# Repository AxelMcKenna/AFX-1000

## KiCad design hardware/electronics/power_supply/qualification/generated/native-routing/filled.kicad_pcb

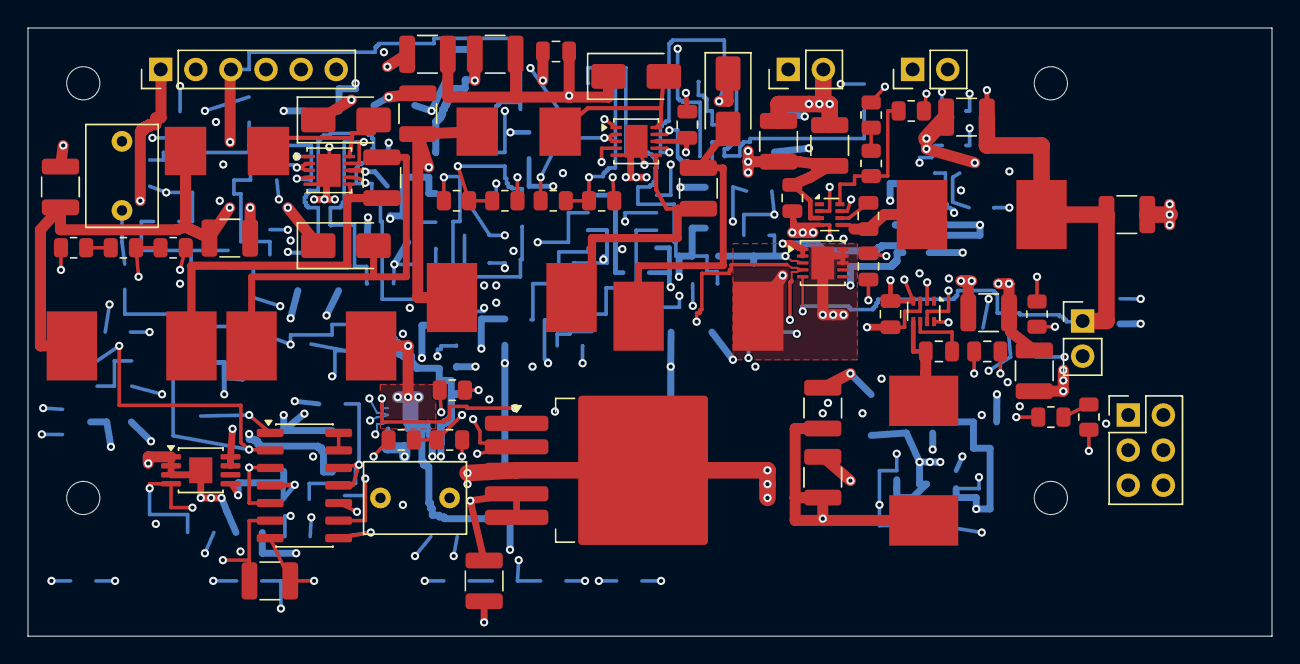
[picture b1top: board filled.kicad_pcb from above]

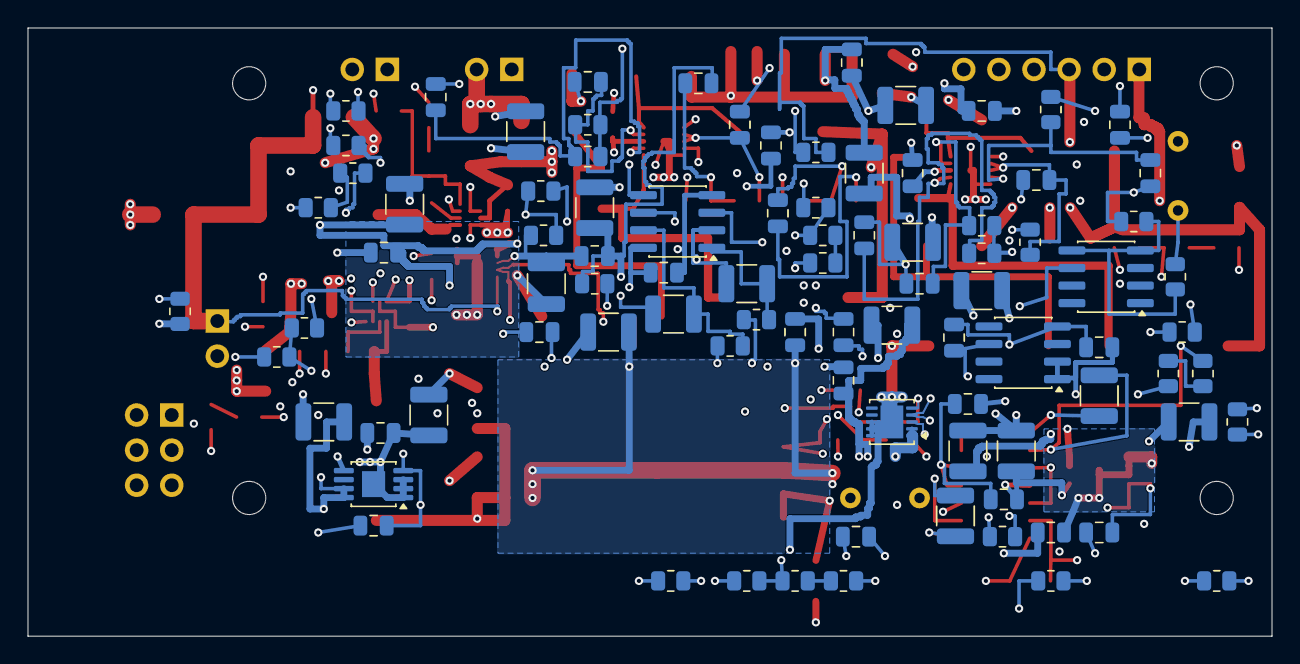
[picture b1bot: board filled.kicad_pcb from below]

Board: 6 copper layers, 90.0 x 44.0 mm, 161 parts (89 on the bottom side), 67 nets.

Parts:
C1, C63: 10uF 63V X7R; C_1210_3225Metric
C2, C3, C5, C6, C8, C9, C37, C42, C47, C52, C57, C64, C65, C67, C68, C70: 22uF 50V X7R; C_1210_3225Metric
C4, C7, C10, C22, C29, C35, C38, C40, C43, C45, C48, C50, C53, C55, C58, C59, C61, C66, C69, C71: 100nF 50V X7R; C_0805_2012Metric
C11, C16, C23, C30, C72: 100nF 16V X7R; C_0805_2012Metric
C12, C14, C73, C75: 68pF 50V C0G 5%; C_0805_2012Metric
C13, C15, C74, C76: 330nF 16V X7R; C_0805_2012Metric
C17: 1uF 16V X7R; C_0805_2012Metric
C18, C19, C25, C26: 22uF 16V X7R; C_1210_3225Metric
C20, C21, C27, C28: 10uF 25V X7R; C_1210_3225Metric
C24: 33nF 16V X7R; C_0805_2012Metric
C31: 2.2uF 16V X7R; C_0805_2012Metric
C32, C33: 1uF film 63V 10% MKS2C041001F00KSSD; C_Rect_L7.2mm_W5.0mm_P5.00mm
C34, C39, C44, C49, C54: 47nF 50V C0G 5%; C_1210_3225Metric
C36, C41, C46, C51, C56: 10uF 50V X7R; C_1210_3225Metric
C60, C62: 1uF 50V X7R; C_0805_2012Metric
D1, D2, D3, D4: SS16-E3/61T; D_SMA
H1, H2, H3, H4: M2_CLEARANCE; M2_Clearance
J1, J3, J5: Header2; PinHeader_1x02_P2.54mm_Vertical
J2: Header6; PinHeader_1x06_P2.54mm_Vertical
J4: Header6; PinHeader_2x03_P2.54mm_Vertical
L1, L6: 33uH 20% SRP7050WA-330M; SRP7050WA
L2, L3, L7, L8: 68uH 20% SRP1050WA-680M; SRP1050WA
L4, L5: 10uH 20% SRP1050WA-100M; SRP1050WA
R1: 300k 0.01% 5ppm; R_0805_2012Metric
R2, R3, R4, R45, R46: 15k 0.01% 5ppm; R_0805_2012Metric
R5, R20, R21, R34, R35: 330k 0.01% 5ppm; R_0805_2012Metric
R6, R7, R49, R50: 4.7k 1%; R_0805_2012Metric
R8, R12: 10k 1%; R_0805_2012Metric
R9, R13: 22k 1%; R_0805_2012Metric
R10: 10.5k 0.01% 5ppm; R_0805_2012Metric
R11, R16: 2k 0.01% 5ppm; R_0805_2012Metric
R14: 12.4k 0.01% 5ppm; R_0805_2012Metric
R15: 100 0.01% 5ppm; R_0805_2012Metric
R17, R19: 1k 1%; R_0805_2012Metric
R18: 100k 1%; R_0805_2012Metric
R22, R27, R30, R31, R36, R41: 100k 0.01% 5ppm; R_0805_2012Metric
R23, R28, R32, R37, R42: 6.8k 1%; R_0805_2012Metric
R24, R38: 9.09k 1%; R_0805_2012Metric
R25, R39, R47: 200k 0.01% 5ppm; R_0805_2012Metric
R26, R40: 180k 0.01% 5ppm; R_0805_2012Metric
R29, R43: 5.62k 1%; R_0805_2012Metric
R33: 2.21k 1%; R_0805_2012Metric
R44: 240k 0.01% 5ppm; R_0805_2012Metric
R48: 54.9k 0.01% 5ppm; R_0805_2012Metric
R51: 10 0.01% 5ppm; R_0805_2012Metric
U1, U13: LT3471EDD#PBF; DFN-10-1EP_3x3mm_P0.5mm_EP1.65x2.38mm
U2, U3: TPS62933FDRLR; SOT-583-8
U4: REF5025EIDR; SOIC-8_3.9x4.9mm_P1.27mm
U5: OPA4192ID; SOIC-14_3.9x8.7mm_P1.27mm
U6: OPA2192ID; SOIC-8_3.9x4.9mm_P1.27mm
U7, U9: LT3080IMS8E#PBF; MSOP-8-1EP_3x3mm_P0.65mm_EP1.68x1.88mm
U8: LT3080IQ#PBF; TO-263-5_TabPin3
U10, U11: LT3090IDD#PBF; DFN-10-1EP_3x3mm_P0.5mm_EP1.65x2.38mm
U12: LT1634AIS8-2.5#PBF; SOIC-8_3.9x4.9mm_P1.27mm

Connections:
/5V_DIG_SRC: C18.1, C19.1, C30.1, J3.1, L4.2, R6.1, R7.1, R10.1, R49.1, R50.1, U4.1, U4.2, U10.5, U11.5
/AGND: C2.2, C3.2, C4.2, C5.2, C6.2, C7.2, C8.2, C9.2, C10.2, C11.2, C13.2, C15.2, C17.2, C18.2, C19.2, C20.2, C21.2, C22.2, C24.2, C25.2, C26.2, C27.2, C28.2, C29.2, C30.2, C31.2, C32.2, C33.2, C35.2, C36.2, C37.2, C38.2, C40.2, C41.2, C42.2, C43.2, C45.2, C46.2, C47.2, C48.2, C50.2, C51.2, C52.2, C53.2, C55.2, C56.2, C57.2, C58.2, C59.2, C60.2, C61.2, C62.2, C64.2, C65.2, C66.2, C67.2, C68.2, C69.2, C70.2, C71.2, C72.2, C74.2, C76.2, D2.1, D4.1, J1.2, J2.2, J3.2, J4.2, J5.1, R3.2, R9.2, R11.2, R13.2, R16.2, R22.2, R24.2, R27.2, R29.2, R31.2, R33.2, R36.2, R38.2, R41.2, R43.2, R45.2, U1.5, U1.11, U2.4, U3.4, U4.4, U5.11, U5.12, U6.8, U10.3, U11.3, U12.6, U13.5, U13.11
/CUK_NODE: C1.2, D2.2, L3.1
/DIG_BST: C16.1, U2.6
/DIG_FB: R11.1, R51.2, U2.8
/DIG_FB_TRIM: R10.2, R51.1
/DIG_SS: C17.1, U2.7
/DIG_SW: C16.2, L4.1, U2.5
/LO_CUK_NODE: C63.2, D4.2, L8.1
/LO_N_FB: C75.2, R46.2, R47.1, U13.4
/LO_N_RMID: R47.2, R48.1
/LO_N_SS: C76.1, R50.2, U13.7
/LO_N_SW: C63.1, L7.2, U13.6
/LO_P_FB: C73.2, R44.2, R45.1, U13.1
/LO_P_SS: C74.1, R49.2, U13.9
/LO_P_SW: D3.2, L6.2, U13.10
/LO_REF_1V: C72.1, R46.1, U13.2, U13.3
/N12_DRIVE: C54.1, R42.1, U6.7
/N12_FB: C54.2, R40.2, R41.1, U6.6
/N12_RMID: R39.2, R40.1
/N12_SET: C55.1, R39.1, R42.2, U11.4
/N12_SRC: C57.1, C58.1, J2.5, R43.1, U11.1, U11.2
/N19_DRIVE: C49.1, R37.1, U6.1
/N19_FB: C49.2, R35.2, R36.1, U6.2
/N19_RMID: R34.2, R35.1
/N19_SET: C50.1, R34.1, R37.2, U10.4
/N19_SRC: C52.1, C53.1, J2.3, R38.1, U10.1, U10.2
/NREF_2V5: R18.1, R19.1, U12.4, U12.5
/NREF_FILTER: C33.1, R19.2, U6.3, U6.5
/P12_DRIVE: C39.1, R28.1, U5.7
/P12_FB: C39.2, R26.2, R27.1, U5.6
/P12_RMID: R25.2, R26.1
/P12_SET: C40.1, R25.1, R28.2, U8.2
/P12_SRC: C42.1, C43.1, J2.4, R29.1, U8.3
/P19_DRIVE: C34.1, R23.1, U5.1
/P19_FB: C34.2, R21.2, R22.1, U5.2
/P19_RMID: R20.2, R21.1
/P19_SET: C35.1, R20.1, R23.2, U7.4
/P19_SRC: C37.1, C38.1, J2.1, R24.1, U7.1, U7.2, U7.3, U7.9
/POWER_READY: J5.2, R8.1, R12.1
/PREF_2V5: C31.1, R17.1, U4.6
/PREF_FILTER: C32.1, R17.2, U5.3, U5.5, U5.10
/PRE_BST: C23.1, U3.6
/PRE_FB: R15.2, R16.1, U3.8
/PRE_RMID: R14.2, R15.1
/PRE_SS: C24.1, U3.7
/PRE_SW: C23.2, L5.1, U3.5
/RAW_N17: C56.1, C67.1, C68.1, C69.1, C75.1, J4.5, L8.2, R48.2, U11.8, U11.9, U11.10, U11.11
/RAW_N22: C8.1, C9.1, C10.1, C14.1, C51.1, C61.1, C62.1, J4.3, L3.2, R5.2, R18.2, U6.4, U10.8, U10.9, U10.10, U10.11
/RAW_N_FB: C14.2, R4.2, R5.1, U1.4
/RAW_N_SS: C15.1, R7.2, U1.7
/RAW_N_SW: C1.1, L2.2, U1.6
/RAW_P17: C41.1, C64.1, C65.1, C66.1, C73.1, D3.1, J4.4, R44.1, U8.4, U8.5
/RAW_P22: C5.1, C6.1, C7.1, C12.1, C36.1, C59.1, C60.1, D1.1, J4.1, R1.1, U5.4, U7.5, U7.7, U7.8
/RAW_P_FB: C12.2, R2.2, R3.1, U1.1
/RAW_P_RMID: R1.2, R2.1
/RAW_P_SS: C13.1, R6.2, U1.9
/RAW_P_SW: D1.2, L1.2, U1.10
/SPARE_OUT: U5.13, U5.14
/SUPPLY_ENABLE: R8.2, R9.1, R12.2, R13.1, U2.2, U3.2
/SW_REF_1V: C11.1, R4.1, U1.2, U1.3
/V5_PRE: C25.1, C26.1, C46.1, J4.6, L5.2, R14.1, U9.7, U9.8
/V5_REG_DRIVE: C44.1, R32.1, U5.8
/V5_REG_FB: C44.2, R30.2, R31.1, U5.9
/V5_REG_SET: C45.1, R30.1, R32.2, U9.4
/V5_REG_SRC: C47.1, C48.1, J2.6, R33.1, U9.1, U9.2, U9.3, U9.9
/VIN_PROTECTED: C2.1, C3.1, C4.1, C20.1, C21.1, C22.1, C27.1, C28.1, C29.1, C70.1, C71.1, J1.1, L1.1, L2.1, L6.1, L7.1, U1.8, U2.3, U3.3, U9.5, U13.8

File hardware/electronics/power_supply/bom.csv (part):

Reference,Part_or_value,Footprint_candidate,Datasheet,Design_note
U1,LT3471EDD#PBF,Package_DFN_QFN:DFN-10-1EP_3x3mm_P0.5mm_EP1.65x2.38mm,https://www.analog.com/media/en/technical-documentation/data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,"EP is ground. Switches rated42V; raw rails are nominal+/-22V, subject to allocated error/ripple."
L1,33uH 20% SRP7050WA-330M,RMX_Power:SRP7050WA,https://www.bourns.com/docs/Product-Datasheets/SRP7050WA.pdf,"E24 selected candidate; retain requirement 33uH 20% Isat>=3A Irms>=1.5A DCR<=0.2ohm. Datasheet Irms/Isat are typical25C entries, not guaranteed minimums; bias, hot DCR, core loss and actual temperature qualification remain open."
L2,68uH 20% SRP1050WA-680M,RMX_Power:SRP1050WA,https://www.bourns.com/docs/Product-Datasheets/SRP1050WA.pdf,"E24 selected candidate; retain requirement 68uH 20% Isat>=3A Irms>=1.5A DCR<=0.2ohm. Datasheet Irms/Isat are typical25C entries, not guaranteed minimums; bias, hot DCR, core loss and actual temperature qualification remain open."
L3,68uH 20% SRP1050WA-680M,RMX_Power:SRP1050WA,https://www.bourns.com/docs/Product-Datasheets/SRP1050WA.pdf,"E24 selected candidate; retain requirement 68uH 20% Isat>=3A Irms>=1.5A DCR<=0.2ohm. Datasheet Irms/Isat are typical25C entries, not guaranteed minimums; bias, hot DCR, core loss and actual temperature qualification remain open."
D1,SS16-E3/61T,Diode_SMD:D_SMA,https://www.vishay.com/docs/88746/ss12.pdf,Vishay60V1A; VF allowance1V includes cold margin; actual leakage/ripple and ringing require qualification.
D2,SS16-E3/61T,Diode_SMD:D_SMA,https://www.vishay.com/docs/88746/ss12.pdf,Vishay60V1A; VF allowance1V includes cold margin; actual leakage/ripple and ringing require qualification.
C1,10uF 63V X7R,Capacitor_SMD:C_1210_3225Metric,,Effective>=2.2uF; RMS ripple>=0.6A required at switching frequency
C2,22uF 50V X7R,Capacitor_SMD:C_1210_3225Metric,,Each effective>=5uF; capacitor RMS/ESR and placement require qualification
C3,22uF 50V X7R,Capacitor_SMD:C_1210_3225Metric,,Each effective>=5uF; capacitor RMS/ESR and placement require qualification
C4,100nF 50V X7R,Capacitor_SMD:C_0805_2012Metric,,
C5,22uF 50V X7R,Capacitor_SMD:C_1210_3225Metric,,Each effective>=5uF; capacitor RMS/ESR and placement require qualification
C6,22uF 50V X7R,Capacitor_SMD:C_1210_3225Metric,,Each effective>=5uF; capacitor RMS/ESR and placement require qualification
C7,100nF 50V X7R,Capacitor_SMD:C_0805_2012Metric,,
C8,22uF 50V X7R,Capacitor_SMD:C_1210_3225Metric,,Each effective>=5uF; capacitor RMS/ESR and placement require qualification
C9,22uF 50V X7R,Capacitor_SMD:C_1210_3225Metric,,Each effective>=5uF; capacitor RMS/ESR and placement require qualification
C10,100nF 50V X7R,Capacitor_SMD:C_0805_2012Metric,,
C11,100nF 16V X7R,Capacitor_SMD:C_0805_2012Metric,,
R1,300k 0.01% 5ppm,Resistor_SMD:R_0805_2012Metric,,
R2,15k 0.01% 5ppm,Resistor_SMD:R_0805_2012Metric,,
R3,15k 0.01% 5ppm,Resistor_SMD:R_0805_2012Metric,,
R4,15k 0.01% 5ppm,Resistor_SMD:R_0805_2012Metric,,
R5,330k 0.01% 5ppm,Resistor_SMD:R_0805_2012Metric,,
C12,68pF 50V C0G 5%,Capacitor_SMD:C_0805_2012Metric,,Initial compensation candidate; manufacturer-model/load-step loop qualification open
R6,4.7k 1%,Resistor_SMD:R_0805_2012Metric,,
C13,330nF 16V X7R,Capacitor_SMD:C_0805_2012Metric,,
C14,68pF 50V C0G 5%,Capacitor_SMD:C_0805_2012Metric,,Initial compensation candidate; manufacturer-model/load-step loop qualification open
R7,4.7k 1%,Resistor_SMD:R_0805_2012Metric,,
C15,330nF 16V X7R,Capacitor_SMD:C_0805_2012Metric,,
U2,TPS62933FDRLR,Package_TO_SOT_SMD:SOT-583-8,https://www.ti.com/lit/ds/symlink/tps62933f.pdf,FCCM; RT floating selects500kHz nominal. Accuracy screen uses0..85C junction range; thermal qualification open.
R8,10k 1%,Resistor_SMD:R_0805_2012Metric,,
R9,22k 1%,Resistor_SMD:R_0805_2012Metric,,
R10,10.5k 0.01% 5ppm,Resistor_SMD:R_0805_2012Metric,,
R11,2k 0.01% 5ppm,Resistor_SMD:R_0805_2012Metric,,
C16,100nF 16V X7R,Capacitor_SMD:C_0805_2012Metric,,
C17,1uF 16V X7R,Capacitor_SMD:C_0805_2012Metric,,"E21 digital slow-start allocation: effective0.8..1.2uF; includes connected E17 bulk in the startup screen. Actual gate sequencing, loop stability and startup require qualification."
L4,10uH 20% SRP1050WA-100M,RMX_Power:SRP1050WA,https://www.bourns.com/docs/Product-Datasheets/SRP1050WA.pdf,"E24 selected candidate; retain requirement 10uH 20% Isat>=6A Irms>=3A DCR<=0.1ohm. Datasheet Irms/Isat are typical25C entries, not guaranteed minimums; bias, hot DCR, core loss and actual temperature qualification remain open."
C18,22uF 16V X7R,Capacitor_SMD:C_1210_3225Metric,,Each effective>=10uF; combined20..60uF target
C19,22uF 16V X7R,Capacitor_SMD:C_1210_3225Metric,,Each effective>=10uF; combined20..60uF target
C20,10uF 25V X7R,Capacitor_SMD:C_1210_3225Metric,,Each effective>=5uF; combined RMS allocation>=1A
C21,10uF 25V X7R,Capacitor_SMD:C_1210_3225Metric,,Each effective>=5uF; combined RMS allocation>=1A
C22,100nF 50V X7R,Capacitor_SMD:C_0805_2012Metric,,
U3,TPS62933FDRLR,Package_TO_SOT_SMD:SOT-583-8,https://www.ti.com/lit/ds/symlink/tps62933f.pdf,FCCM; RT floating selects500kHz nominal. Accuracy screen uses0..85C junction range; thermal qualification open.
R12,10k 1%,Resistor_SMD:R_0805_2012Metric,,
R13,22k 1%,Resistor_SMD:R_0805_2012Metric,,
R14,12.4k 0.01% 5ppm,Resistor_SMD:R_0805_2012Metric,,
R15,100 0.01% 5ppm,Resistor_SMD:R_0805_2012Metric,,
R16,2k 0.01% 5ppm,Resistor_SMD:R_0805_2012Metric,,
C23,100nF 16V X7R,Capacitor_SMD:C_0805_2012Metric,,
C24,33nF 16V X7R,Capacitor_SMD:C_0805_2012Metric,,
L5,10uH 20% SRP1050WA-100M,RMX_Power:SRP1050WA,https://www.bourns.com/docs/Product-Datasheets/SRP1050WA.pdf,"E24 selected candidate; retain requirement 10uH 20% Isat>=6A Irms>=3A DCR<=0.1ohm. Datasheet Irms/Isat are typical25C entries, not guaranteed minimums; bias, hot DCR, core loss and actual temperature qualification remain open."
C25,22uF 16V X7R,Capacitor_SMD:C_1210_3225Metric,,Each effective>=10uF; combined20..60uF target
C26,22uF 16V X7R,Capacitor_SMD:C_1210_3225Metric,,Each effective>=10uF; combined20..60uF target
C27,10uF 25V X7R,Capacitor_SMD:C_1210_3225Metric,,Each effective>=5uF; combined RMS allocation>=1A
C28,10uF 25V X7R,Capacitor_SMD:C_1210_3225Metric,,Each effective>=5uF; combined RMS allocation>=1A
C29,100nF 50V X7R,Capacitor_SMD:C_0805_2012Metric,,
U4,REF5025EIDR,Package_SO:SOIC-8_3.9x4.9mm_P1.27mm,https://www.ti.com/lit/ds/symlink/ref50.pdf,
C30,100nF 16V X7R,Capacitor_SMD:C_0805_2012Metric,,
C31,2.2uF 16V X7R,Capacitor_SMD:C_0805_2012Metric,,Effective>=1uF
R17,1k 1%,Resistor_SMD:R_0805_2012Metric,,
C32,1uF film 63V 10% MKS2C041001F00KSSD,Capacitor_THT:C_Rect_L7.2mm_W5.0mm_P5.00mm,https://www.wima.de/wp-content/uploads/media/d_WIMA_MKS_2.pdf,"E24 candidate WIMA MKS2, 1uF63V10%, body7.2x5x10mm/pitch5mm; leakage/assembly qualification open."
U12,LT1634AIS8-2.5#PBF,Package_SO:SOIC-8_3.9x4.9mm_P1.27mm,https://www.analog.com/media/en/technical-documentation/data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,Industrial A grade. Do not connect pin4 to system ground.
R18,100k 1%,Resistor_SMD:R_0805_2012Metric,,
R19,1k 1%,Resistor_SMD:R_0805_2012Metric,,
C33,1uF film 63V 10% MKS2C041001F00KSSD,Capacitor_THT:C_Rect_L7.2mm_W5.0mm_P5.00mm,https://www.wima.de/wp-content/uploads/media/d_WIMA_MKS_2.pdf,"E24 candidate WIMA MKS2, 1uF63V10%, body7.2x5x10mm/pitch5mm; leakage/assembly qualification open."
R20,330k 0.01% 5ppm,Resistor_SMD:R_0805_2012Metric,,
R21,330k 0.01% 5ppm,Resistor_SMD:R_0805_2012Metric,,
R22,100k 0.01% 5ppm,Resistor_SMD:R_0805_2012Metric,,
R23,6.8k 1%,Resistor_SMD:R_0805_2012Metric,,Limit SET clamp current; Kelvin DC feedback is after this resistor
C34,47nF 50V C0G 5%,Capacitor_SMD:C_1210_3225Metric,,Local HF feedback bypasses remote SET pole; finite loop/PCB qualification open
C35,100nF 50V X7R,Capacitor_SMD:C_0805_2012Metric,,Effective50..120nF for target-source loop screen
R24,9.09k 1%,Resistor_SMD:R_0805_2012Metric,,Minimum-load/discharge resistor; qualify power rating and thermal derating
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
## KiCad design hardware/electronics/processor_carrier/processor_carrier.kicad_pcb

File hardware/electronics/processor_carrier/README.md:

# E19 processor carrier — routed prototype

This circuit connects the Seed3 processor, ten knob inputs, E18 control hub,
E09 converter and E11 bypass controller for the **standalone external-converter
firmware profile**. It also exposes interfaces for the planned LED, touch,
angle-sensor and SD boards. Those interfaces do not complete those boards.

The 76-part native KiCad schematic and 150 × 65 mm four-layer PCB pass electrical,
routing, schematic parity and open-connection checks with zero violations.
An independent verifier checks all 40 module pins, ten knob channels,
connector pin order against fresh exports of the other four board schematics,
and the current F04 firmware assignments. See
[verification.json](generated/verification.json) and
[connector-map.csv](generated/connector-map.csv).

The processor now occupies the front slot on normal-height sockets. E18 shifts
2 mm left to clear the lower spacer fixings. Eight mounting holes and copper
keepouts are implemented, and the PCB-derived module, component, solder-tail,
fastener and USB allocations feed the A05 housing model. Full electronics
placement, wiring, thermal behavior and physical fit remain unverified.
This is not a fabrication package.

The [A05/E19 review package](../../releases/README.md#processor-and-housing-review-a05-e19)
captures the current processor/input/output placement and housing sources.

The ten 10 kΩ linear pots use the module's analog 3.3 V output, a 1 kΩ series
resistor, 100 nF shunt capacitor and 1 MΩ bleed per ADC input. Digital 3.3 V and
analog 3.3 V remain separate; module AGND and DGND join on the carrier.
[Conditional DC/RC screens](generated/passive-screen.json) do not verify ADC
acquisition, leakage, accuracy, noise or the full supply budget. Passive MPNs
and capacitor effective values remain to be selected and qualified.

The 40-pad library pattern preserves Electrosmith's supplied pad centers and
numbering: 2.54 mm pitch, 15.24 mm between rows and 1.7 mm pads. The unmodified
source and MIT license are in `vendor/`. The carrier adapts the original holes
to the chosen pair of
[SSW-120-02-G-S sockets](https://www.samtec.com/products/ssw-120-02-g-s). Samtec's
[single-row layout](https://suddendocs.samtec.com/prints/ssw-s.pdf) calls for
1.04 mm nominal holes, now used in the carrier. Finished-hole/plating tolerances,
socket insertion and the physical stack remain unqualified.
The Seed3 module's own PCB hole dimensions are separate from the carrier socket
holes. Legacy module graphics and STEP models are removed. Actual component
MPNs, a USB pigtail and physical tolerances must meet the documented allocations.

The ten ADC filter networks use short bottom-side connections beside the module
pins. Raw wiper traces escape through exact socket-pitch midpoints before joining
the harness fanout. In1 is a continuous AGND plane, with explicit copper exclusions
around all eight fasteners. Native connectivity removes redundant vias during
generation; the independent verifier then checks the saved PCB again.

J1 matches E17 J4 directly: pin 1 protected `5V_DIG`, pin 2 ground. It must not
receive raw 12 V. J6 requires a split harness: pins 1/2 feed E09 J4 pins 2/3;
pins 1/3/4/5/6 connect E09 J5 pins 1/2/3/4/6. E09 J4 pin 1 (`V5_REG`) comes from
the analog supply, not J6. Never join the module's 3.3 V outputs to a separate
regulator output. J2 reset and J4 bypass use the documented E18 signal aliases.
All E19 wiring is external-profile only; the onboard bring-up profile assigns
several of these processor pins differently.

Run from the repository root with Python 3.11+ and KiCad 10:

```sh
python3 -m hardware.electronics.processor_carrier.generate
python3 -m hardware.electronics.processor_carrier.board --kicad-cli /path/to/kicad-cli
python3 -m hardware.electronics.processor_carrier.verify --kicad-cli /path/to/kicad-cli
```

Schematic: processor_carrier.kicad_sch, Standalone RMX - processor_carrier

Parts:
C1: 22uF 25V X7R; C_1210_3225Metric
C2, C4, C6, C11, C12, C13, C14, C15, C16, C17, C18, C19, C20: 100nF 16V X7R; C_0805_2012Metric
C3: 1uF 16V X7R; C_0805_2012Metric
C5: 4.7uF 16V X7R; C_0805_2012Metric
J1, J7, J8: Header2; PinHeader_1x02_P2.54mm_Vertical
J2, J4, J5: Header5; PinHeader_1x05_P2.54mm_Vertical
J3, J6: Header6; PinHeader_1x06_P2.54mm_Vertical
J9, J10: Header4; PinHeader_1x04_P2.54mm_Vertical
J11, J12: Header8; PinHeader_1x08_P2.54mm_Vertical
J20, J21, J22, J23, J24, J25, J26, J27, J28, J29: Header3; PinHeader_1x03_P2.54mm_Vertical
R1: 0.47R 1% 1W; R_2512_6332Metric
R2: 10k 1%; R_0805_2012Metric
R3, R4, R5, R6: 100k 1%; R_0805_2012Metric
R10, R11, R12, R13, R14, R15, R16, R17, R18, R19, R20: 33R 1%; R_0805_2012Metric
R31, R32, R33, R34, R35, R36, R37, R38, R39, R40: 1k 1%; R_0805_2012Metric
R41, R42, R43, R44, R45, R46, R47, R48, R49, R50: 1M 1%; R_0805_2012Metric
U1: DaisySeed3; Seed3_Socket40

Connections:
/5V_DIG: J1.1, J11.2, R1.1
/ADC_DATA: J5.4, U1.32 (D25_ADC_DATA)
/AGND: C1.2, C2.2, C3.2, C4.2, C5.2, C6.2, C11.2, C12.2, C13.2, C14.2, C15.2, C16.2, C17.2, C18.2, C19.2, C20.2, J1.2, J2.1, J3.1, J4.1, J5.1, J6.1, J7.1, J8.1, J9.1, J10.1, J11.1, J11.8, J12.1, J20.1, J21.1, J22.1, J23.1, J24.1, J25.1, J26.1, J27.1, J28.1, J29.1, R3.2, R4.2, R5.2, R6.2, R41.2, R42.2, R43.2, R44.2, R45.2, R46.2, R47.2, R48.2, R49.2, R50.2, U1.20 (AGND), U1.40 (DGND)
/ANALOG_OK: J4.4, J6.6
/ARMED: J3.5, R5.1, U1.37 (D30_ARMED)
/BCLK: J5.2, U1.35 (D28_BCLK)
/BYPASS_SENSE: J3.6, J4.3
/CODEC_RUN: J2.5, J6.5, R6.1, U1.1 (D0)
/DAC_DATA: J5.5, R14.2
/DAC_DATA_SRC: R14.1, U1.33 (D26_DAC_DATA)
/GAIN_REQ: J3.4, R4.1, U1.10 (D9)
/HEARTBEAT: J3.2, U1.14 (D13)
/INPUT_READY: J4.5, J7.2
/LED_BLANK: J11.7, R2.1, R13.2
/LED_BLANK_SRC: R13.1, U1.15 (D14)
/LED_MOSI: J11.4, R12.2
/LED_MOSI_SRC: R12.1, U1.11 (D10)
/LED_SCK: J11.5, R11.2
/LED_SCK_SRC: R11.1, U1.9 (D8)
/LED_XLAT: J11.6, R10.2
/LED_XLAT_SRC: R10.1, U1.8 (D7)
/MCU_PERMIT: J3.3, R3.1, U1.36 (D29_PERMIT)
/MODE_SEND_RETURN: J4.2, J8.2
/POT_ADC_00: C11.1, R31.2, R41.1, U1.22 (D15)
/POT_ADC_01: C12.1, R32.2, R42.1, U1.23 (D16)
/POT_ADC_02: C13.1, R33.2, R43.1, U1.24 (D17)
/POT_ADC_03: C14.1, R34.2, R44.1, U1.25 (D18)
/POT_ADC_04: C15.1, R35.2, R45.1, U1.26 (D19)
/POT_ADC_05: C16.1, R36.2, R46.1, U1.27 (D20)
/POT_ADC_06: C17.1, R37.2, R47.1, U1.28 (D21)
/POT_ADC_07: C18.1, R38.2, R48.1, U1.29 (D22)
/POT_ADC_08: C19.1, R39.2, R49.1, U1.30 (D23)
/POT_ADC_09: C20.1, R40.2, R50.1, U1.31 (D24)
/POT_RAW_00: J20.2, R31.1
/POT_RAW_01: J21.2, R32.1
/POT_RAW_02: J22.2, R33.1
/POT_RAW_03: J23.2, R34.1
/POT_RAW_04: J24.2, R35.1
/POT_RAW_05: J25.2, R36.1
/POT_RAW_06: J26.2, R37.1
/POT_RAW_07: J27.2, R38.1
/POT_RAW_08: J28.2, R39.1
/POT_RAW_09: J29.2, R40.1
/SCL: J2.3, J6.3, J9.3, J10.3, U1.12 (D11)
/SDA: J2.4, J6.4, J9.4, J10.4, U1.13 (D12)
/SDMMC_CLK: J12.8, R20.2
/SDMMC_CLK_SRC: R20.1, U1.7 (D6)
/SDMMC_CMD: J12.7, R19.2
/SDMMC_CMD_SRC: R19.1, U1.6 (D5)
/SDMMC_D0: J12.3, R15.2
/SDMMC_D0_SRC: R15.1, U1.5 (D4)
/SDMMC_D1: J12.4, R16.2
/SDMMC_D1_SRC: R16.1, U1.4 (D3)
/SDMMC_D2: J12.5, R17.2
/SDMMC_D2_SRC: R17.1, U1.3 (D2)
/SDMMC_D3: J12.6, R18.2
/SDMMC_D3_SRC: R18.1, U1.2 (D1)
/SEED_VIN: C1.1, C2.1, R1.2, U1.39 (VIN)
/V3V3_ANALOG: C3.1, C4.1, J20.3, J21.3, J22.3, J23.3, J24.3, J25.3, J26.3, J27.3, J28.3, J29.3, U1.21 (3V3_ANALOG)
/V3V3_IO: C5.1, C6.1, J2.2, J6.2, J9.2, J10.2, J11.3, J12.2, R2.2, U1.38 (3V3_DIGITAL)
/WS: J5.3, U1.34 (D27_WS)

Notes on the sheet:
E19 - external-profile Seed3 processor carrier.40 module pins,10 analog pots,control-hub/codec/relay/LED/sensor/SD interfaces.
3.3V outputs are separate: analog pin21 excites pots; digital pin38 powers shared logic. AGND and DGND join on carrier.
Proposed150x65mm carrier: front-slot Seed placement and2mm E18 daughterboard shift still require PCB/CAD implementation.
No whole-bus/3.3V load, USB partial-power/backfeed, ADC acquisition/accuracy, SDMMC SI or physical fit approval. No fabrication release.

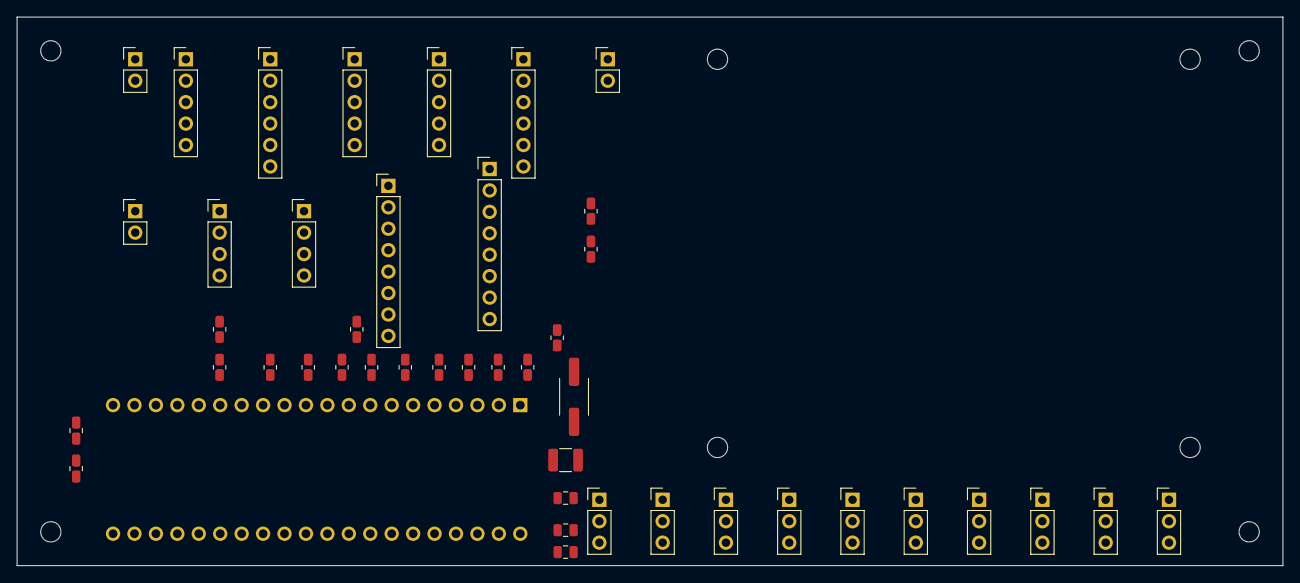
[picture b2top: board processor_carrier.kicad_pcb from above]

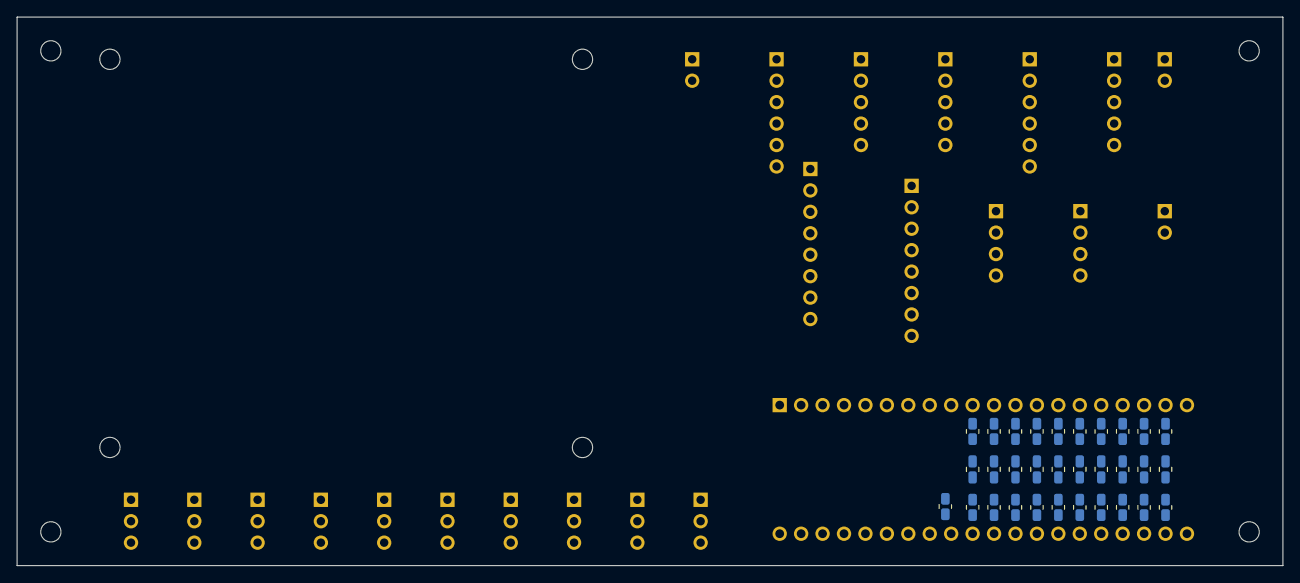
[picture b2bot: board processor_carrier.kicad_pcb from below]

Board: 4 copper layers, 150.0 x 65.0 mm, 84 parts (31 on the bottom side), 61 nets, no tracks yet.

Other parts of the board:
H1, H2, H3, H4: M2_CLEARANCE; M2_Insert_Clearance
H5, H6, H7, H8: M2_CLEARANCE; M2_Daughter

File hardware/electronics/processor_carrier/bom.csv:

Reference,Part_or_value,Footprint,Source,Note
U1,DaisySeed3,RMX_Carrier:Seed3_Socket40,https://daisy.nyc3.cdn.digitaloceanspaces.com/products/seed3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,External firmware profile only. Carrier assembly includes Seed3 and2xSSW-120-02-G-S sockets; clip socket solder tails<=3mm including solder.
J1,Header2,Connector_PinHeader_2.54mm:PinHeader_1x02_P2.54mm_Vertical,,"Protected digital supply from E17 J4, same pin order; no raw12V input."
J2,Header5,Connector_PinHeader_2.54mm:PinHeader_1x05_P2.54mm_Vertical,,E18 J5; CODEC_RUN alias CONTROL_RESET_N; external profile only.
J3,Header6,Connector_PinHeader_2.54mm:PinHeader_1x06_P2.54mm_Vertical,,E11 J2 six-pin order; bypass sense passes to E18 rear header.
J4,Header5,Connector_PinHeader_2.54mm:PinHeader_1x05_P2.54mm_Vertical,,E18 J4; BYPASS_SENSE alias MANUAL_BYPASS.
J5,Header5,Connector_PinHeader_2.54mm:PinHeader_1x05_P2.54mm_Vertical,,E09 J3; DAC_DATA source damping at carrier.
J6,Header6,Connector_PinHeader_2.54mm:PinHeader_1x06_P2.54mm_Vertical,,Split harness to E09 J4 IO power/J5 bus/status. Do not join independent3.3V outputs.
J7,Header2,Connector_PinHeader_2.54mm:PinHeader_1x02_P2.54mm_Vertical,,E11 J6 status.
J8,Header2,Connector_PinHeader_2.54mm:PinHeader_1x02_P2.54mm_Vertical,,Rear maintained CONNECTION contact: closed=send/return.
J9,Header4,Connector_PinHeader_2.54mm:PinHeader_1x04_P2.54mm_Vertical,,Trill Craft bus; include module pull-ups in whole-bus budget.
J10,Header4,Connector_PinHeader_2.54mm:PinHeader_1x04_P2.54mm_Vertical,,AS5600 board bus; sensor board incomplete.
J11,Header8,Connector_PinHeader_2.54mm:PinHeader_1x08_P2.54mm_Vertical,,TLC5947 board interface; receiving BLANK pull-up still required on future LED board.
J12,Header8,Connector_PinHeader_2.54mm:PinHeader_1x08_P2.54mm_Vertical,,"Reserved SDMMC interface. Card-power budget, socket/detect, filesystem and physical SI unfinished."
R1,0.47R 1% 1W,Resistor_SMD:R_2512_6332Metric,,"Source resistor budget uses0.5A; physical load, thermal and startup qualification open."
R2,10k 1%,Resistor_SMD:R_0805_2012Metric,,
R3,100k 1%,Resistor_SMD:R_0805_2012Metric,,
R4,100k 1%,Resistor_SMD:R_0805_2012Metric,,
R5,100k 1%,Resistor_SMD:R_0805_2012Metric,,
R6,100k 1%,Resistor_SMD:R_0805_2012Metric,,
R10,33R 1%,Resistor_SMD:R_0805_2012Metric,,Source damping; physical edge/SI qualification unfinished.
R11,33R 1%,Resistor_SMD:R_0805_2012Metric,,Source damping; physical edge/SI qualification unfinished.
R12,33R 1%,Resistor_SMD:R_0805_2012Metric,,Source damping; physical edge/SI qualification unfinished.
R13,33R 1%,Resistor_SMD:R_0805_2012Metric,,Source damping; physical edge/SI qualification unfinished.
R14,33R 1%,Resistor_SMD:R_0805_2012Metric,,Source damping; physical edge/SI qualification unfinished.
R15,33R 1%,Resistor_SMD:R_0805_2012Metric,,Source damping; physical edge/SI qualification unfinished.
R16,33R 1%,Resistor_SMD:R_0805_2012Metric,,Source damping; physical edge/SI qualification unfinished.
R17,33R 1%,Resistor_SMD:R_0805_2012Metric,,Source damping; physical edge/SI qualification unfinished.
R18,33R 1%,Resistor_SMD:R_0805_2012Metric,,Source damping; physical edge/SI qualification unfinished.
R19,33R 1%,Resistor_SMD:R_0805_2012Metric,,Source damping; physical edge/SI qualification unfinished.
R20,33R 1%,Resistor_SMD:R_0805_2012Metric,,Source damping; physical edge/SI qualification unfinished.
C1,22uF 25V X7R,Capacitor_SMD:C_1210_3225Metric,,
C2,100nF 16V X7R,Capacitor_SMD:C_0805_2012Metric,,
C3,1uF 16V X7R,Capacitor_SMD:C_0805_2012Metric,,
C4,100nF 16V X7R,Capacitor_SMD:C_0805_2012Metric,,
C5,4.7uF 16V X7R,Capacitor_SMD:C_0805_2012Metric,,
C6,100nF 16V X7R,Capacitor_SMD:C_0805_2012Metric,,
J20,Header3,Connector_PinHeader_2.54mm:PinHeader_1x03_P2.54mm_Vertical,,input: 10k linear pot; excitation is module analog3.3V output.
R31,1k 1%,Resistor_SMD:R_0805_2012Metric,,
C11,100nF 16V X7R,Capacitor_SMD:C_0805_2012Metric,,
R41,1M 1%,Resistor_SMD:R_0805_2012Metric,,Open-wiper bleed; does not provide wire-fault detection.
J21,Header3,Connector_PinHeader_2.54mm:PinHeader_1x03_P2.54mm_Vertical,,output: 10k linear pot; excitation is module analog3.3V output.
R32,1k 1%,Resistor_SMD:R_0805_2012Metric,,
C12,100nF 16V X7R,Capacitor_SMD:C_0805_2012Metric,,
R42,1M 1%,Resistor_SMD:R_0805_2012Metric,,Open-wiper bleed; does not provide wire-fault detection.
J22,Header3,Connector_PinHeader_2.54mm:PinHeader_1x03_P2.54mm_Vertical,,low: 10k linear pot; excitation is module analog3.3V output.
R33,1k 1%,Resistor_SMD:R_0805_2012Metric,,
C13,100nF 16V X7R,Capacitor_SMD:C_0805_2012Metric,,
R43,1M 1%,Resistor_SMD:R_0805_2012Metric,,Open-wiper bleed; does not provide wire-fault detection.
J23,Header3,Connector_PinHeader_2.54mm:PinHeader_1x03_P2.54mm_Vertical,,mid: 10k linear pot; excitation is module analog3.3V output.
R34,1k 1%,Resistor_SMD:R_0805_2012Metric,,
C14,100nF 16V X7R,Capacitor_SMD:C_0805_2012Metric,,
R44,1M 1%,Resistor_SMD:R_0805_2012Metric,,Open-wiper bleed; does not provide wire-fault detection.
J24,Header3,Connector_PinHeader_2.54mm:PinHeader_1x03_P2.54mm_Vertical,,high: 10k linear pot; excitation is module analog3.3V output.
R35,1k 1%,Resistor_SMD:R_0805_2012Metric,,
C15,100nF 16V X7R,Capacitor_SMD:C_0805_2012Metric,,
R45,1M 1%,Resistor_SMD:R_0805_2012Metric,,Open-wiper bleed; does not provide wire-fault detection.
J25,Header3,Connector_PinHeader_2.54mm:PinHeader_1x03_P2.54mm_Vertical,,scene_depth: 10k linear pot; excitation is module analog3.3V output.
R36,1k 1%,Resistor_SMD:R_0805_2012Metric,,
C16,100nF 16V X7R,Capacitor_SMD:C_0805_2012Metric,,
R46,1M 1%,Resistor_SMD:R_0805_2012Metric,,Open-wiper bleed; does not provide wire-fault detection.
J26,Header3,Connector_PinHeader_2.54mm:PinHeader_1x03_P2.54mm_Vertical,,x_level: 10k linear pot; excitation is module analog3.3V output.
R37,1k 1%,Resistor_SMD:R_0805_2012Metric,,
C17,100nF 16V X7R,Capacitor_SMD:C_0805_2012Metric,,
R47,1M 1%,Resistor_SMD:R_0805_2012Metric,,Open-wiper bleed; does not provide wire-fault detection.
J27,Header3,Connector_PinHeader_2.54mm:PinHeader_1x03_P2.54mm_Vertical,,x_pitch: 10k linear pot; excitation is module analog3.3V output.
R38,1k 1%,Resistor_SMD:R_0805_2012Metric,,
C18,100nF 16V X7R,Capacitor_SMD:C_0805_2012Metric,,
R48,1M 1%,Resistor_SMD:R_0805_2012Metric,,Open-wiper bleed; does not provide wire-fault detection.
J28,Header3,Connector_PinHeader_2.54mm:PinHeader_1x03_P2.54mm_Vertical,,scene_time: 10k linear pot; excitation is module analog3.3V output.
R39,1k 1%,Resistor_SMD:R_0805_2012Metric,,
C19,100nF 16V X7R,Capacitor_SMD:C_0805_2012Metric,,
R49,1M 1%,Resistor_SMD:R_0805_2012Metric,,Open-wiper bleed; does not provide wire-fault detection.
J29,Header3,Connector_PinHeader_2.54mm:PinHeader_1x03_P2.54mm_Vertical,,scene_resonance: 10k linear pot; excitation is module analog3.3V output.
R40,1k 1%,Resistor_SMD:R_0805_2012Metric,,
C20,100nF 16V X7R,Capacitor_SMD:C_0805_2012Metric,,
R50,1M 1%,Resistor_SMD:R_0805_2012Metric,,Open-wiper bleed; does not provide wire-fault detection.
